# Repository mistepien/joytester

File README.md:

# joytester
Joytester for testing of Atari-like+ joysticks

Joytester for testing Atari-like joysticks -- tests also FIRE2 nd FIRE3 in C64 and Amiga/Atari mode.

More about Amiga/Atari and C64 modes: <a href="https://wiki.icomp.de/wiki/File:JoystickMod.jpg">schematic of universal joystick</a>.

<b>Populate only one of U1 or U2, never both!</b>

SW3 is redundand.

You can use the <a href="https://github.com/mistepien/joytester/tree/main/production">gerber file</a> to order the PCB.

Here you have <a href="https://github.com/mistepien/joytester/blob/main/joytester.pdf
">the schematic file</a> to find out how does it work.

BOM:
| Qty	| Reference(s) | Description |
|-----|--------------|-------------|
|10 | D1, D2, D3, D4, D5, D6, D7, D8, D9, D10 | LEDs 3mm |  
|10 | R1, R2, R3, R4, R5, R6, R7, R8, R9, R10 | resisors for D1...D10 |
|3 | R11, R12, R13 | 10KΩ pull-up/pull-down resistors |
| 2 | R14, R15 | 5K1Ω resistors for J3 USB C power-only socket |
|1 | J1| DB9 Male Connector ( eg. <a href="https://www.tme.eu/pl/en/details/ld09p13a4gx00lf/d-sub-plugs-and-sockets/amphenol-communications-solutions/">LD09P13A4GX00LF Amphenol</a>) |
|1 | J2 | USB B socket |
|1 | J3 | USB C power-only socket (eg.  <a href="https://www.tme.eu/pl/en/details/usb4125-gf-a/usb-ieee1394-connectors/gct/">USB4125-GF-A GCT</a> ) |
|1 | J4 | USB B Mini socket |
|1 | J5 | USB B Micro socket |
|1 | U1 | DIP14 socket (width 7.62mm) + 4070 IC or 4030 IC XOR Gates|
|1 | U2 | DIP14 socket (width 7.62mm) + 74HC86 IC XOR Gates |
|2| C1, C2 | decoupling capacitors for U2 | 
|2| C3, C4 | decoupling capacitors for U1 | 
|2 | SW1, SW2 | SPDT switches or 3x1 2.54mm pinheaders |
|1 | SW3 | SPDT switch, terminal pitch: 4.7mm |

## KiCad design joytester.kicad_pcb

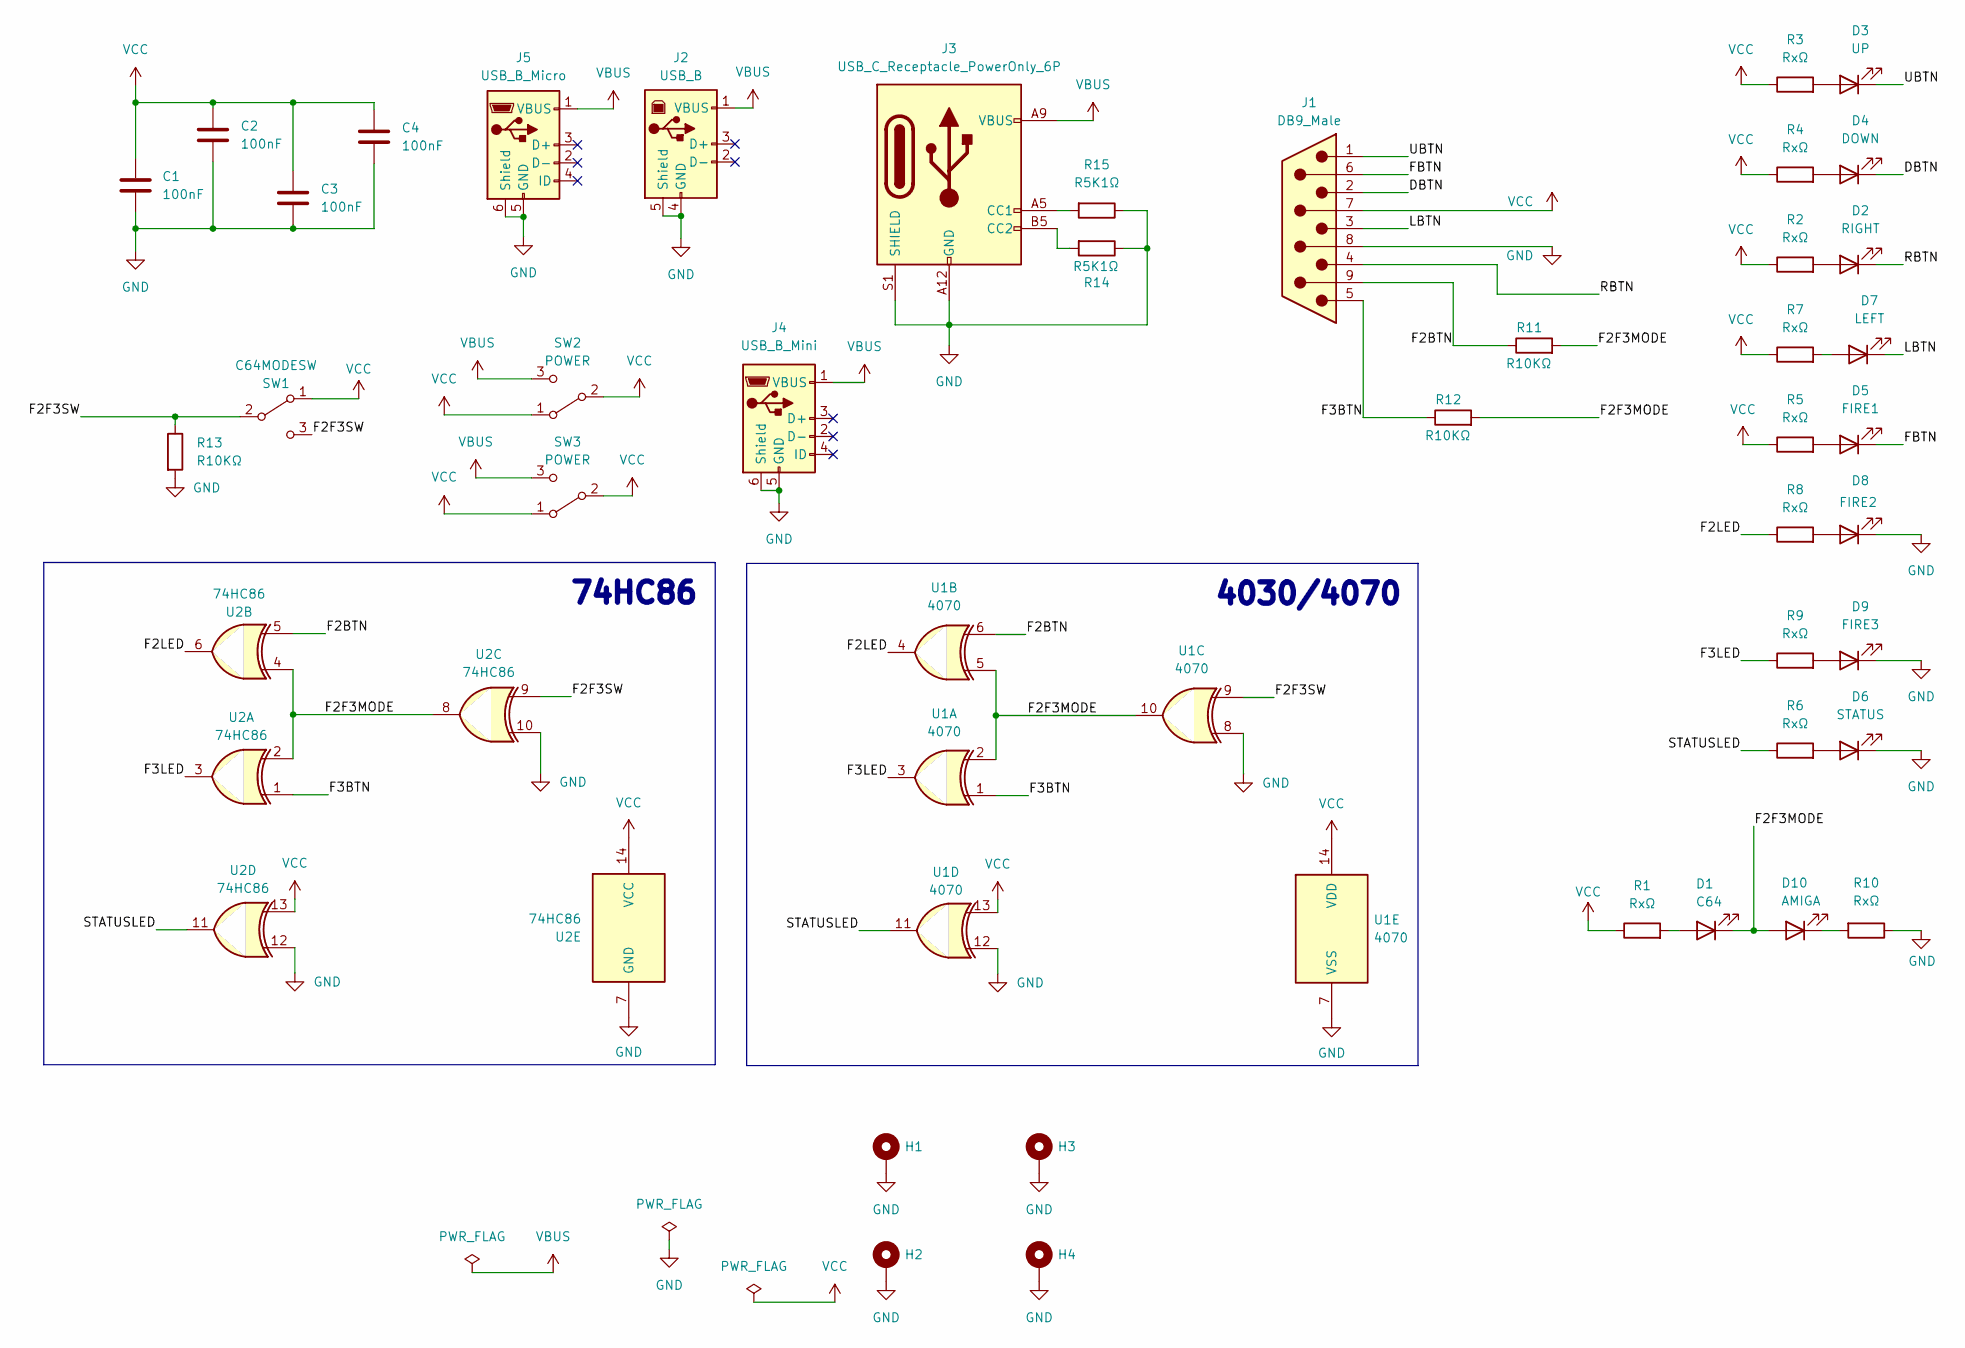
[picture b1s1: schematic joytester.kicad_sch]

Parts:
C1, C2, C3, C4: 100nF; C_Disc_D3.8mm_W2.6mm_P2.50mm
D1: C64; LED_D3.0mm_Oval
D2: RIGHT; LED_D3.0mm_Oval
D3: UP; LED_D3.0mm_Oval
D4: DOWN; LED_D3.0mm_Oval
D5: FIRE1; LED_D3.0mm_Oval
D6: STATUS; LED_D3.0mm_Oval
D7: LEFT; LED_D3.0mm_Oval
D8: FIRE2; LED_D3.0mm_Oval
D9: FIRE3; LED_D3.0mm_Oval
D10: AMIGA; LED_D3.0mm_Oval
H1, H2, H3, H4: MountingHole; MountingHole_3.5mm_Pad_Via
J1: DB9_Male; DSUB-9_Male_Horizontal_P2.77x2.84mm_EdgePinOffset7.70mm_Hou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
J2: USB_B; USB_B_Lumberg_2411_02_Horizontal_Oval_Versatile
J3: USB_C_Receptacle_PowerOnly_6P; GCT_USB4125-GF-A
J4: USB_B_Mini; UBM5BRDM144DLFSNL
J5: USB_B_Micro; USB_Micro-B_Amphenol_10118194_Horizontal
R1, R2, R3, R4, R5, R6, R7, R8, R9, R10: RxΩ; R_Axial_DIN0207_L6.3mm_D2.5mm_P10.16mm_Horizontal_Oval
R11, R12, R13: R10KΩ; R_Axial_DIN0207_L6.3mm_D2.5mm_P10.16mm_Horizontal_Oval
R14, R15: R5K1Ω; R_Axial_DIN0207_L6.3mm_D2.5mm_P10.16mm_Horizontal_Oval
SW1: C64MODESW; E-Switch-EG1218-Manufacturer_Recommended_Oval
SW2: POWER; E-Switch-EG1218-Manufacturer_Recommended_Oval
SW3: POWER; 100SP1T1B4M2QE
U1: 4070; DIP-14_W7.62mm_Socket_LongPads
U2: 74HC86; DIP-14_W7.62mm_Socket_LongPads

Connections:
/DBTN: D4.1 (K), J1.2
/F2BTN: J1.9, R11.1, U1.6, U2.5
/F2F3MODE: D1.1 (K), D10.2 (A), R11.2, R12.2, U1.2, U1.5, U1.10, U2.2, U2.4, U2.8
/F2F3SW: R13.1, SW1.2 (B), SW1.3 (C), U1.9, U2.9
/F2LED: R8.1, U1.4, U2.6
/F3BTN: J1.5, R12.1, U1.1, U2.1
/F3LED: R9.1, U1.3, U2.3
/FBTN: D5.1 (K), J1.6
/LBTN: D7.1 (K), J1.3
/RBTN: D2.1 (K), J1.4
/STATUSLED: R6.1, U1.11, U2.11
/UBTN: D3.1 (K), J1.1
GND: C1.2, C2.2, C3.2, C4.2, D6.1 (K), D8.1 (K), D9.1 (K), H1.1, H2.1, H3.1, H4.1, J1.8, J2.4 (GND), J2.5 (Shield), J3.A12 (GND), J3.B12 (GND), J3.S1 (SHIELD), J4.5 (GND), J4.6 (Shield), J5.5 (GND), J5.6 (Shield), R10.1, R13.2, R14.1, R15.1, U1.7 (VSS), U1.8, U1.12, U2.7 (GND), U2.10, U2.12
unnamed: D1.2 (A), R1.2
unnamed: D2.2 (A), R2.2
unnamed: D3.2 (A), R3.2
unnamed: D4.2 (A), R4.2
unnamed: D5.2 (A), R5.2
unnamed: D6.2 (A), R6.2
unnamed: D7.2 (A), R7.2
unnamed: D8.2 (A), R8.2
unnamed: D9.2 (A), R9.2
unnamed: D10.1 (K), R10.2
unnamed: J3.A5 (CC1), R15.2
unnamed: J3.B5 (CC2), R14.2
VBUS: J2.1 (VBUS), J3.A9 (VBUS), J3.B9 (VBUS), J4.1 (VBUS), J5.1 (VBUS), SW2.3 (C), SW3.3 (C)
VCC: C1.1, C2.1, C3.1, C4.1, J1.7, R1.1, R2.1, R3.1, R4.1, R5.1, R7.1, SW1.1 (A), SW2.1 (A), SW2.2 (B), SW3.1 (A), SW3.2 (B), U1.13, U1.14 (VDD), U2.13, U2.14 (VCC)

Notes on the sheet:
74HC86
4030/4070

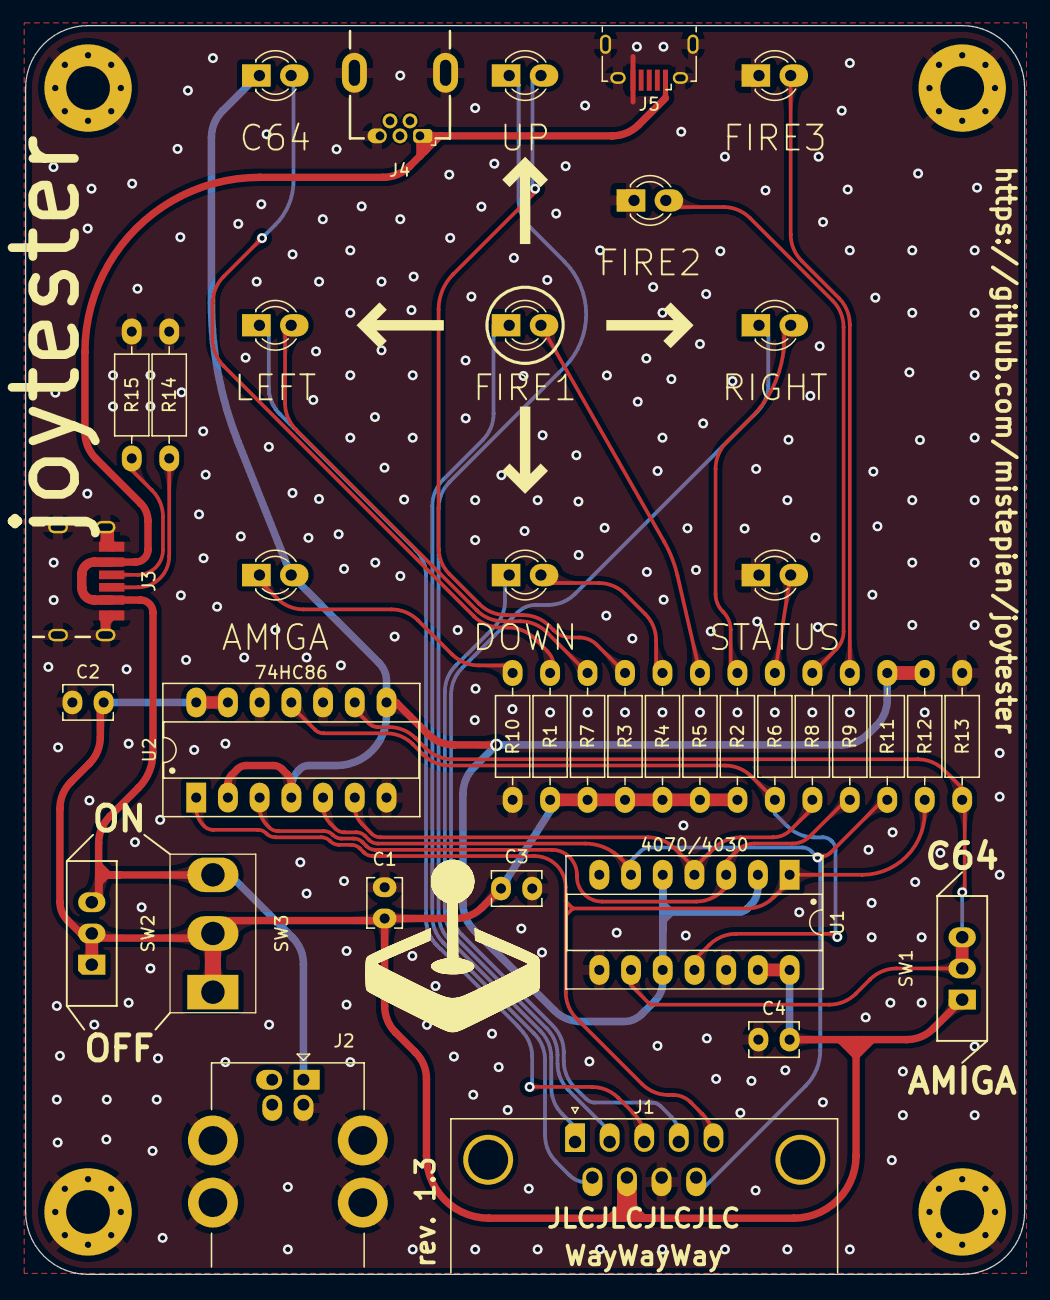
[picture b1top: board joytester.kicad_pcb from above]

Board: 2 copper layers, 80.0 x 100.0 mm, 43 parts (0 on the bottom side), 27 nets.

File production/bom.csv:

Designator,Footprint,Quantity,Value,LCSC Part #
"C1, C2, C3, C4",C_Disc_D3.8mm_W2.6mm_P2.50mm,4,100nF,
D1,LED_D3.0mm_Oval,1,C64,
D10,LED_D3.0mm_Oval,1,AMIGA,
D2,LED_D3.0mm_Oval,1,RIGHT,
D3,LED_D3.0mm_Oval,1,UP,
D4,LED_D3.0mm_Oval,1,DOWN,
D5,LED_D3.0mm_Oval,1,FIRE1,
D6,LED_D3.0mm_Oval,1,STATUS,
D7,LED_D3.0mm_Oval,1,LEFT,
D8,LED_D3.0mm_Oval,1,FIRE2,
D9,LED_D3.0mm_Oval,1,FIRE3,
J1,DSUB-9_Male_Horizontal_P2.77x2.84mm_EdgePinOffset7.70mm_Housed_MountingHolesOffset9.12mm,1,DB9_Male,
J2,USB_B_Lumberg_2411_02_Horizontal_Oval_Versatile,1,USB_B,
J3,GCT_USB4125-GF-A,1,USB_C_Receptacle_PowerOnly_6P,
J4,UBM5BRDM144DLFSNL,1,USB_B_Mini,
J5,USB_Micro-B_Amphenol_10118194_Horizontal,1,USB_B_Micro,
"R1, R10, R2, R3, R4, R5, R6, R7, R8, R9",R_Axial_DIN0207_L6.3mm_D2.5mm_P10.16mm_Horizontal_Oval,10,RxΩ,
"R11, R12, R13",R_Axial_DIN0207_L6.3mm_D2.5mm_P10.16mm_Horizontal_Oval,3,R10KΩ,
"R14, R15",R_Axial_DIN0207_L6.3mm_D2.5mm_P10.16mm_Horizontal_Oval,2,R5K1Ω,
SW1,E-Switch-EG1218-Manufacturer_Recommended_Oval,1,C64MODESW,
SW2,E-Switch-EG1218-Manufacturer_Recommended_Oval,1,POWER,
SW3,100SP1T1B4M2QE,1,POWER,
U1,DIP-14_W7.62mm_Socket_LongPads,1,4070,
U2,DIP-14_W7.62mm_Socket_LongPads,1,74HC86,

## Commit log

2025-05-10 Upload images
2025-05-10 upload of files
2025-05-10 upload of schematic
2025-05-10 update of schematic file
2025-09-02 minor update
2025-10-06 update of Micro USB footprint
2026-05-09 Fix order
